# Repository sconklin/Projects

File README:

A holding repo for various projects, mostly ones which have hardware.

I'll try to maintain this list of what's under the top directory:

* VGA-switch - a VGA disconnect switch box for testing monitor hotplug

* custom-eagle-libs - Libraries for parts I've added to Eagle CAD for these projects

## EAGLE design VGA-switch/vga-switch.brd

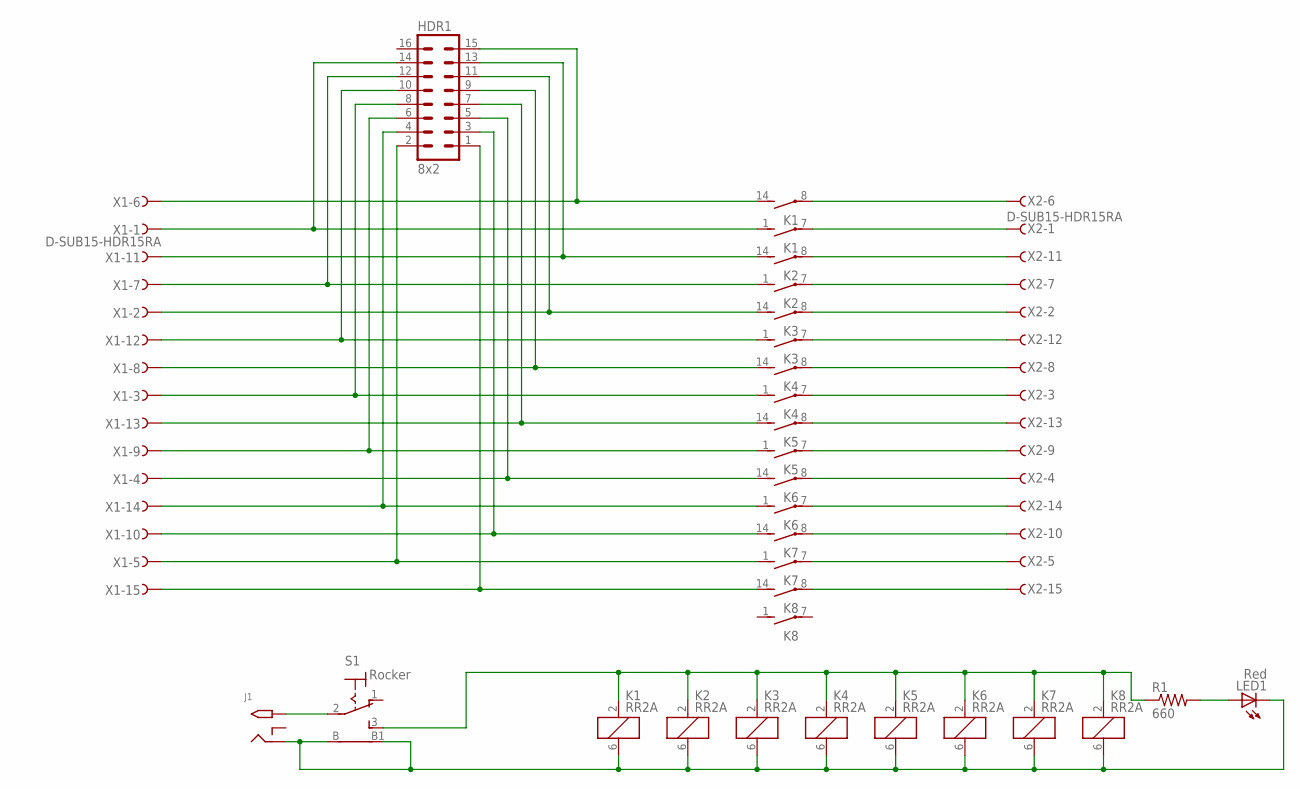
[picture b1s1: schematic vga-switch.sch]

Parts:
HDR1: 8x2; MA08-2
J1: 2.1MMJACKTHM; PJ-102A
K1, K2, K3, K4, K5, K6, K7, K8: RR2A
LED1: Red; LED5MM
R1: 660; 0207/10
S1: Rocker; ROCKERSWITCH
X1, X2: D-SUB15-HDR15RA; HDR15RA

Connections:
unnamed: J1.TIP, S1.2
unnamed: J1.RING, K1.6 (2), K2.6 (2), K3.6 (2), K4.6 (2), K5.6 (2), K6.6 (2), K7.6 (2), K8.6 (2), LED1.K (C), S1.B, S1.B1
unnamed: HDR1.15, K1.14 (S), X1.6
unnamed: K1.2 (1), K2.2 (1), K3.2 (1), K4.2 (1), K5.2 (1), K6.2 (1), K7.2 (1), K8.2 (1), R1.1, S1.3 (S)
unnamed: LED1.A, R1.2
unnamed: HDR1.14, K1.1 (S), X1.1
unnamed: HDR1.13, K2.14 (S), X1.11
unnamed: HDR1.12, K2.1 (S), X1.7
unnamed: HDR1.11, K3.14 (S), X1.2
unnamed: HDR1.10, K3.1 (S), X1.12
unnamed: HDR1.9, K4.14 (S), X1.8
unnamed: HDR1.8, K4.1 (S), X1.3
unnamed: HDR1.7, K5.14 (S), X1.13
unnamed: HDR1.6, K5.1 (S), X1.9
unnamed: HDR1.5, K6.14 (S), X1.4
unnamed: HDR1.4, K6.1 (S), X1.14
unnamed: HDR1.3, K7.14 (S), X1.10
unnamed: HDR1.2, K7.1 (S), X1.5
unnamed: HDR1.1, K8.14 (S), X1.15
unnamed: K1.8, X2.6
unnamed: K1.7, X2.1
unnamed: K2.8, X2.11
unnamed: K2.7, X2.7
unnamed: K3.8, X2.2
unnamed: K3.7, X2.12
unnamed: K4.8, X2.8
unnamed: K4.7, X2.3
unnamed: K5.8, X2.13
unnamed: K5.7, X2.9
unnamed: K6.8, X2.4
unnamed: K6.7, X2.14
unnamed: K7.8, X2.10
unnamed: K7.7, X2.5
unnamed: K8.8, X2.15

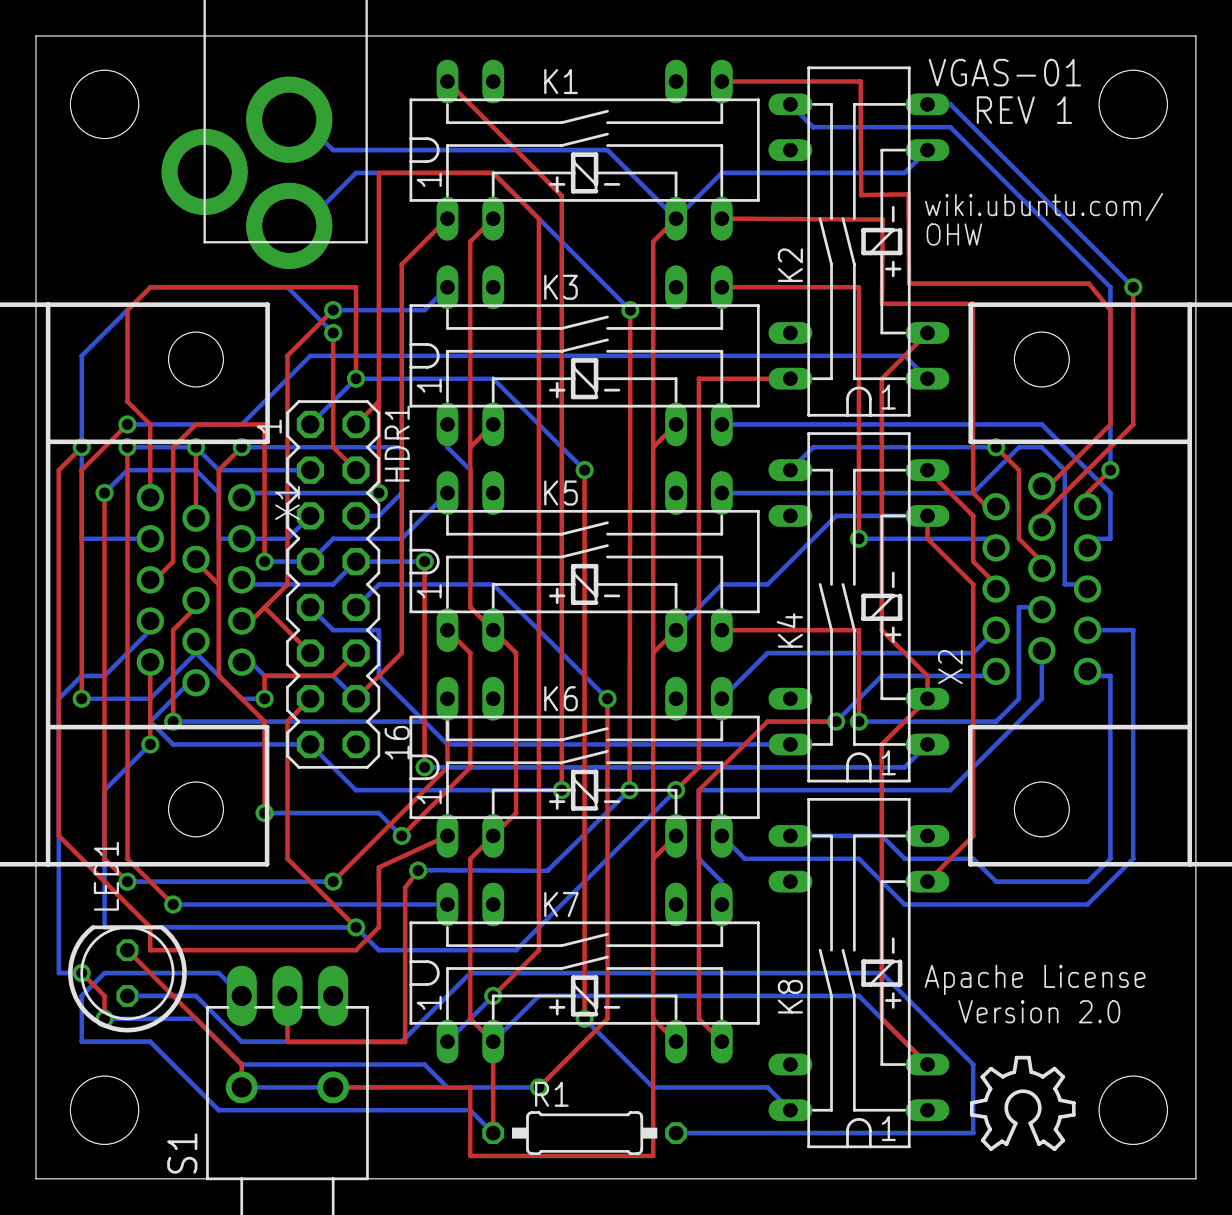
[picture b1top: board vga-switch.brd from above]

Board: 2 copper layers, 64.4 x 63.5 mm, 17 parts (0 on the bottom side), 34 nets.

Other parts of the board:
U$1: OSHW_8X200_NOTEXT
U$2: UBUNTU-LOGO

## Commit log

2011-12-31 Initial checkin
2011-12-31 directory rename
2011-12-31 moar datasheets
2011-12-31 added README
2012-01-01 toggle switch data sheet
2012-01-01 added BOM
2012-01-01 BOM change
2012-01-01 a few components
2012-01-06 Start a list of compatible parts
2012-01-06 changed parts from final qualification
2012-01-06 added more components
2012-01-06 added switch to library
2012-01-06 Added a notes file
2012-01-06 Started wiring
2012-01-07 notes update
2012-01-07 first pass at routing
2012-01-19 board changes, layout, and logo work
2012-01-20 added logos
2012-01-20 remove unneeded logo files
2012-02-08 Added license
2012-02-08 Added license text to board
2012-02-09 Generated output for order
2012-02-09 Started the case design
2012-02-13 more progress on the enclosure
2012-02-13 BOM as ordered for first run
2012-02-18 final BOM
2012-02-18 adjusted enclosure based on actual board
2012-02-19 tweak encolsure
2012-02-22 Improve board holder, and make minor size adjustments
2012-02-22 stl files for case top and bottom, initial commit
2012-02-28 Corrected part number for LED
2012-02-28 Revision to rev 2
    Changes for rev 2:
    There was a via under the power switch which could short to the switch frame.
    This has been moved, and an exclusion zone has been added on the top layer where the switch frame is.
    Added URL to the silkscreen
    Changed rev number on silkscreen
2012-02-28 script to move output files after creation
2012-04-17 tweak board thickness
2012-04-17 Add some photos of th eprototype
2012-04-17 Add some case images exported from openscad
2012-04-17 Add adafruit library for good measure
2012-04-17 Latest antitronics lib changes
2012-04-17 Notes to self about allowable hole sizes for our vendor
2012-07-05 add various arduino projects

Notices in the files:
VGA-switch/vga-switch.brd:
Apache License
